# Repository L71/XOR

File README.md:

XOR
===

XOR logic gate based noise generator. 2x oscillators with voltage control, 3 oscillators with manual control only.
Two outputs, first one from VCO1 and two other oscillators, the second one adds VCO2 and another manually controlled oscillator into the mix.

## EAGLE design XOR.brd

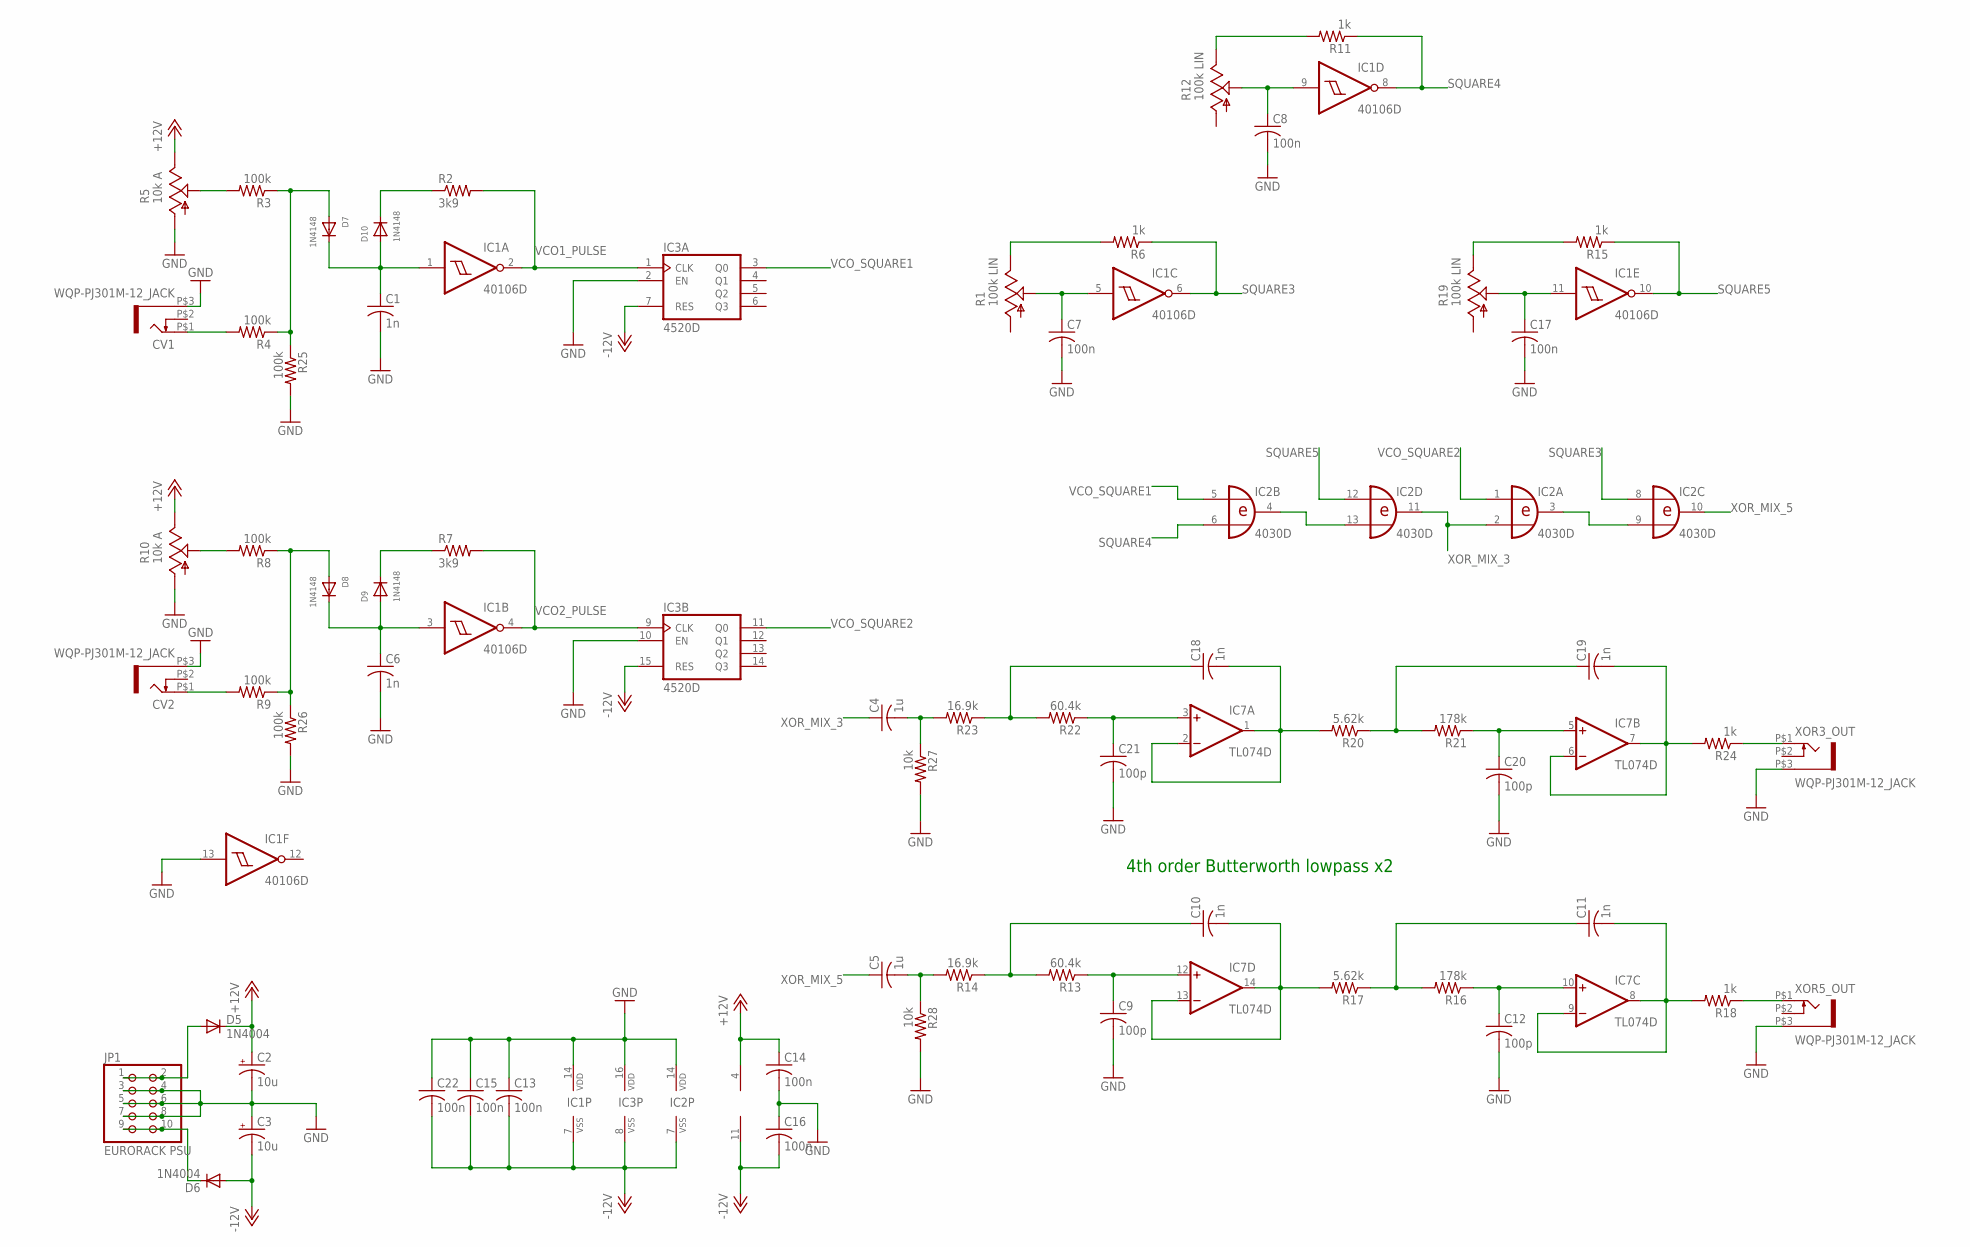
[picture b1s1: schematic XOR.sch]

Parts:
C1, C6, C10, C11, C18, C19: 1n; C0603K
C2, C3: 10u; PANASONIC_D
C4, C5: 1u; C0603K
C7, C8, C13, C14, C15, C16, C17, C22: 100n; C0603K
C9, C12, C20, C21: 100p; C0603K
CV1, CV2: WQP-PJ301M-12_JACK
D5, D6: 1N4004; DO214AA
D7, D8, D9, D10: 1N4148; SOD-323F
IC1: 40106D; SO14
IC2: 4030D; SO14
IC3: 4520D; SO16
IC7: TL074D; SO14
JP1: EURORACK PSU; 2X05
R1, R12, R19: 100k LIN; ALPS_POT_VERTICAL
R2, R7: 3k9; R0603
R3, R4, R8, R9, R25, R26: 100k; R0603
R5, R10: 10k A; ALPS_POT_VERTICAL
R6, R11, R15, R18, R24: 1k; R0603
R13, R22: 60.4k; R0603
R14, R23: 16.9k; R0603
R16, R21: 178k; R0603
R17, R20: 5.62k; R0603
R27, R28: 10k; R0603
XOR3_OUT, XOR5_OUT: WQP-PJ301M-12_JACK

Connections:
+12V: C2.+, C14.1, D5.C, IC7.4 (V+), R5.P$1 (E), R10.P$1 (E)
-12V: C3.-, C13.2, C15.2, C16.2, C22.2, D6.A, IC1.7 (VSS), IC2.7 (VSS), IC3.7 (RES), IC3.8 (VSS), IC3.15 (RES), IC7.11 (V-)
GND: C1.2, C2.-, C3.+, C6.2, C7.2, C8.2, C9.2, C12.2, C13.1, C14.2, C15.1, C16.1, C17.2, C20.2, C21.2, C22.1, CV1.P$3 (1), CV2.P$3 (1), IC1.13 (I), IC1.14 (VDD), IC2.14 (VDD), IC3.2 (EN), IC3.10 (EN), IC3.16 (VDD), JP1.3, JP1.4, JP1.5, JP1.6, JP1.7, JP1.8, R5.P$3 (A), R10.P$3 (A), R25.2, R26.2, R27.2, R28.2, XOR3_OUT.P$3 (1), XOR5_OUT.P$3 (1)
unnamed: R3.2, R5.P$2 (S)
unnamed: CV1.P$1 (2), R4.2
unnamed: D7.A, R3.1, R4.1, R25.1
unnamed: C1.1, D7.C, D10.A, IC1.1 (I)
unnamed: D10.C, R2.1
unnamed: R1.P$1 (E), R6.2
unnamed: R8.2, R10.P$2 (S)
unnamed: D6.C, JP1.9, JP1.10
unnamed: D5.A, JP1.1, JP1.2
unnamed: IC2.3 (O), IC2.9 (I1)
unnamed: R11.2, R12.P$1 (E)
unnamed: C6.1, D8.C, D9.A, IC1.3 (I)
unnamed: C7.1, IC1.5 (I), R1.P$2 (S)
unnamed: D9.C, R7.1
unnamed: C12.1, IC7.10 (+IN), R16.1
unnamed: D8.A, R8.1, R9.1, R26.1
unnamed: C10.2, IC7.13 (-IN), IC7.14 (OUT), R17.2
unnamed: CV2.P$1 (2), R9.2
unnamed: C8.1, IC1.9 (I), R12.P$2 (S)
unnamed: C10.1, R13.2, R14.1
unnamed: C9.1, IC7.12 (+IN), R13.1
unnamed: R18.1, XOR5_OUT.P$1 (2)
unnamed: C17.1, IC1.11 (I), R19.P$2 (S)
unnamed: IC2.4 (O), IC2.13 (I1)
unnamed: R15.2, R19.P$1 (E)
unnamed: C18.1, R22.2, R23.1
unnamed: C18.2, IC7.1 (OUT), IC7.2 (-IN), R20.2
unnamed: C21.1, IC7.3 (+IN), R22.1
unnamed: C11.1, R16.2, R17.1
unnamed: C11.2, IC7.8 (OUT), IC7.9 (-IN), R18.2
unnamed: C4.2, R23.2, R27.1
unnamed: C19.1, R20.1, R21.2
unnamed: C20.1, IC7.5 (+IN), R21.1
unnamed: C19.2, IC7.6 (-IN), IC7.7 (OUT), R24.2
unnamed: R24.1, XOR3_OUT.P$1 (2)
unnamed: C5.2, R14.2, R28.1
SQUARE3: IC1.6 (O), IC2.8 (I0), R6.1
SQUARE4: IC1.8 (O), IC2.6 (I1), R11.1
SQUARE5: IC1.10 (O), IC2.12 (I0), R15.1
VCO1_PULSE: IC1.2 (O), IC3.1 (CLK), R2.2
VCO2_PULSE: IC1.4 (O), IC3.9 (CLK), R7.2
VCO_SQUARE1: IC2.5 (I0), IC3.3 (Q0)
VCO_SQUARE2: IC2.1 (I0), IC3.11 (Q0)
XOR_MIX_3: C4.1, IC2.2 (I1), IC2.11 (O)
XOR_MIX_5: C5.1, IC2.10 (O)

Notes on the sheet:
4th order Butterworth lowpass x2

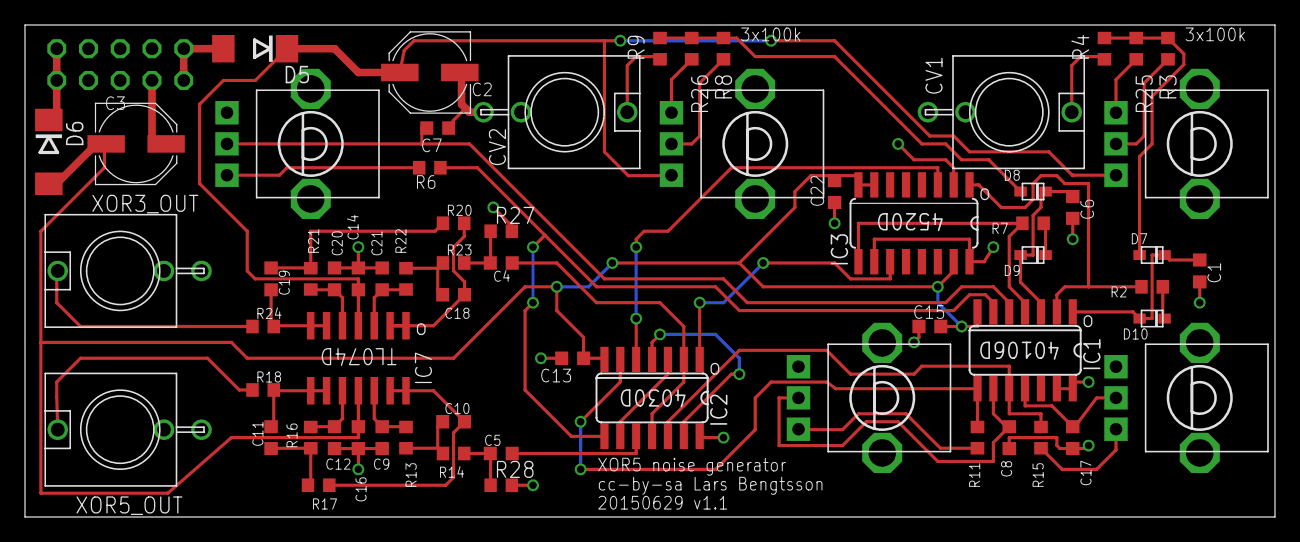
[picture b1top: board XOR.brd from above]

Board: 2 copper layers, 100.0 x 39.4 mm, 65 parts (1 on the bottom side), 48 nets.

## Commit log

2015-06-06 Initial upload.
2015-06-06 added decoupling caps at logic ICs.
2015-06-06 initial upload of board file.
2015-06-07 Changed PSU diode type/footprint. Not fits DO214 package types. PCB: moved ICs a bit, better fit for CV in jack 1.
2015-06-07 Initial commit of panel. (Ponoko specs .SVG).
2015-06-07 did Object-to-path on the text.
2015-06-11 Changed order in which oscillators are XORed together. Use bigger footprint for PSU smoothing caps. Moved XOR IC a bit & rerouted.
2015-06-11 Updated panel to reflect changes in XORing order of oscillators.
2015-06-29 Added 2x10k resistors that pulls the filter inputs to ground (got DC offset problem on the filter outputs without them).
2015-06-29 Added dot at pin 1 of the ICs.
2015-08-22 Updated readme.
2016-04-06 Updated artwork a bit, added algorithm info to panel. Adjusted holes. Should fit well in racks w 3mm screw rails now.

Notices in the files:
XOR.brd:
cc-by-sa Lars Bengtsson
cc-by-sa 2015 Lars Bengtsson
